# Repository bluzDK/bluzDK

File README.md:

Bluz DK Hardware Files
==========
Bluz is a Development Kit (DK) that implements the Wiring language and talks to the [Particle](https://www.particle.io/) cloud through Bluetooth Low Energy. It can be accessed through a REST API and programmed from a Web IDE.

These files have been made available online through a [Creative Commons Attribution-ShareAlike 3.0](http://creativecommons.org/licenses/by-sa/3.0/) license.

You are welcome to distribute, remix, and use these files for commercial purposes. If you do so, please attribute the original design to Bluz both on the website and on the physical packaging of the product or in the instruction manual. All derivative works must be published under the same or a similar license.

All items are subject to change over time as the product is designed, so make sure you are always looking at the latest information by pulling often.

##Sections
<b>BOM</b>: Current Bill of Materials for bluz.

<b>Datasheets</b>: Datasheets for all major parts on the board, including the nrf51822 and the MDBT40 module that it uses.

<b>HW Design</b>: Schematics, board layouts, and other design files.

<b>HW Libraries</b>: Eagle CAD libraries for the components used on Bluz DK.

<b>Pin Mapping</b>: Pin mapping diagram for Bluz.

##Tech Specs
<p>Hardware</p>
<ul>
    <li>Nordic Semiconductor nRF51822 SoC</li>
    <li>ARM Cortex M0, 16MHz</li>
    <li>32KB RAM, 256KB FLASH</li>
    <li>Bluetooth LE 4.1</li>
    <li>10 bit ADC</li>
    <li>256KB External FLASH</li>
    <li>3.0V-6V (3.3V compatible)</li>
</ul>
<p>Power Consumption</p>
<ul>
    <li>Connected/Standby: 60uA</li>
    <li>Transmitting Max: 18mA</li>
</ul>
<p>Typical Range (subject to environment):</p>
<ul>
    <li>Indoors: 60-100 feet</li>
    <li>Outdoors: 150-200 feet</li>
</ul>
<p>Software</p>
<ul>
    <li>Spark Web IDE</li>
    <li>Wiring (same as Arduino)</li>
    <li>Native C/C++ Programming</li>
    <li>GCC ARM</li>
    <li>Assembly (if you're that bold)</li>
</ul>
<p>Cloud</p>
<ul>
    <li>Spark Connected</li>
    <li>IFTTT Integrated</li>
    <li>IPv6 Support</li>
    <li>Remote programmable through Spark Cloud</li>
    <li>Control via REST API</li>
</ul>

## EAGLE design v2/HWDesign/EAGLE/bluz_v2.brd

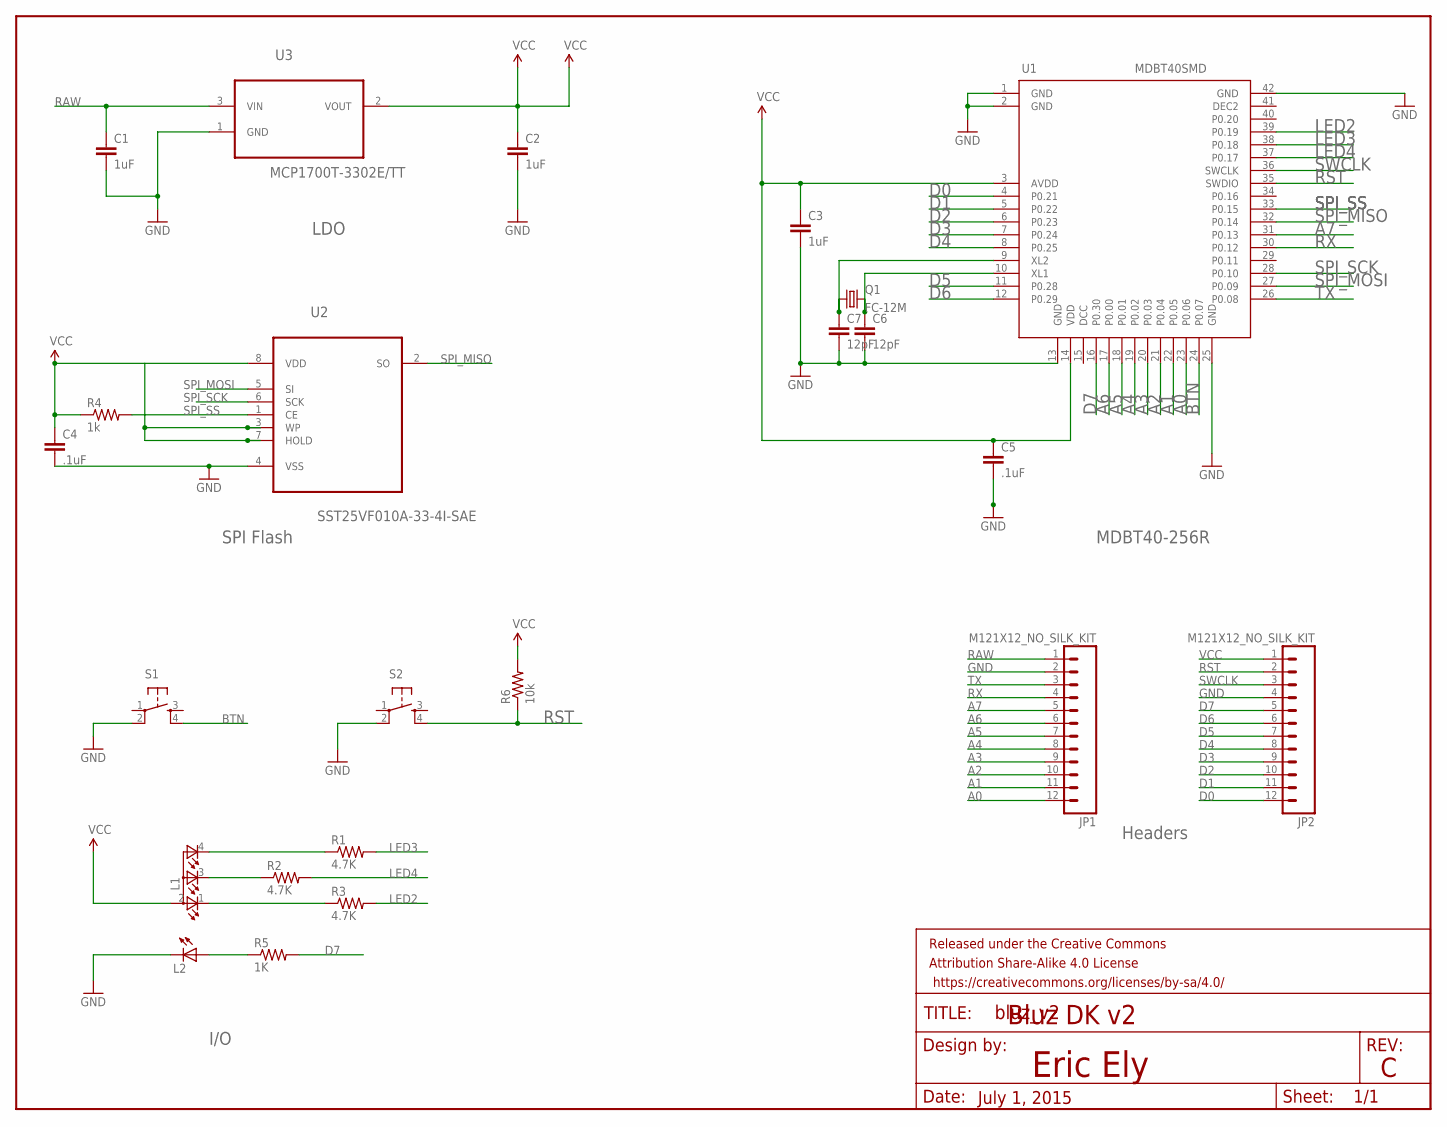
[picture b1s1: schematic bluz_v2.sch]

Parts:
C1, C2, C3: 1uF; 0603-CAP
C4, C5: .1uF; 0603-CAP
C6, C7: 12pF; 0603-CAP
FRAME1: FRAME-LETTER; CREATIVE_COMMONS
JP1, JP2: M121X12_NO_SILK_KIT; 1X12_NO_SILK_KIT
L1: TOPLED-3PLCC; P-LCC-4-3
L2: LEDCHIP-LED0603; CHIP-LED0603
Q1: FC-12M
R1, R2, R3: 4.7K; 0603-RES
R4: 1k; 0603-RES
R5: 1K; 0603-RES
R6: 10k; 0603-RES
S1, S2: TAC_SWITCHSMD; TACTILE_SWITCH_SMD
U1: MDBT40SMD; MDBT40
U2: SST25VF010A-33-4I-SAE; SOIC127P600X175-8N
U3: MCP1700T-3302E/TT; SOT95P237X112-3N

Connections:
A0: JP1.12, U1.23 (P0.06)
A1: JP1.11, U1.22 (P0.05)
A2: JP1.10, U1.21 (P0.04)
A3: JP1.9, U1.20 (P0.03)
A4: JP1.8, U1.19 (P0.02)
A5: JP1.7, U1.18 (P0.01)
A6: JP1.6, U1.17 (P0.00)
A7: JP1.5, U1.31 (P0.13)
BTN: S1.4, U1.24 (P0.07)
D0: JP2.12, U1.4 (P0.21)
D1: JP2.11, U1.5 (P0.22)
D2: JP2.10, U1.6 (P0.23)
D3: JP2.9, U1.7 (P0.24)
D4: JP2.8, U1.8 (P0.25)
D5: JP2.7, U1.11 (P0.28)
D6: JP2.6, U1.12 (P0.29)
D7: JP2.5, R5.2, U1.16 (P0.30)
GND: C1.2, C2.2, C3.2, C4.2, C5.2, C6.2, C7.2, JP1.2, JP2.4, L2.C, S1.2, S2.2, U1.1 (GND), U1.2 (GND), U1.13 (GND), U1.25 (GND), U1.42 (GND), U2.4 (VSS), U3.1 (GND)
LED2: R3.2, U1.39 (P0.19)
LED3: R1.2, U1.38 (P0.18)
LED4: R2.2, U1.37 (P0.17)
unnamed: C7.1, Q1.1, U1.9 (XL2)
unnamed: C6.1, Q1.2, U1.10 (XL1)
unnamed: L2.A, R5.1
unnamed: L1.1 (CRED), R3.1
unnamed: L1.3 (CBLUE), R2.1
unnamed: L1.4 (CGREEN), R1.1
RAW: C1.1, JP1.1, U3.3 (VIN)
RST: JP2.2, R6.1, S2.4, U1.35 (SWDIO)
RX: JP1.4, U1.30 (P0.12)
SPI_MISO: U1.32 (P0.14), U2.2 (SO)
SPI_MOSI: U1.27 (P0.09), U2.5 (SI)
SPI_SCK: U1.28 (P0.10), U2.6 (SCK)
SPI_SS: R4.2, U1.33 (P0.15), U2.1 (CE)
SWCLK: JP2.3, U1.36 (SWCLK)
TX: JP1.3, U1.26 (P0.08)
VCC: C2.1, C3.1, C4.1, C5.1, JP2.1, L1.2 (A2), R4.1, R6.2, U1.3 (AVDD), U1.14 (VDD), U2.3 (WP), U2.7 (HOLD), U2.8 (VDD), U3.2 (VOUT)

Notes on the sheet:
LDO
SPI Flash
I/O
Headers
MDBT40-256R
Eric Ely
Bluz DK v2
July 1, 2015

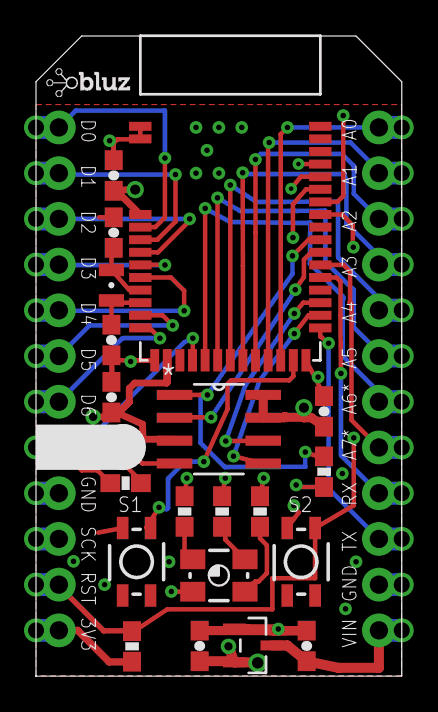
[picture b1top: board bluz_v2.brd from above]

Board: 2 copper layers, 20.3 x 35.6 mm, 26 parts (1 on the bottom side), 37 nets.

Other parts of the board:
U$1: BLUZE_LOGO_LOW_RES
U$2: MAKE_X2

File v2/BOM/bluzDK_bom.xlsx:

Part(s) | Package | Value | Description | Qty | Manufacturer | Mfg. Part Number | Data Sheet | Notes
U1 | SMD |  | nrf51822 module with 32K RAM | 1 | Raytac | MDBT40-256R | data
U2 | SOIC-8 | 2Mb | 2Mb SPI Flash | 1 | Microcip | SST25VF020B-80-4I-SAE | data
U3 | SOT-23-3 |  | Linear regulator with 3.3V output, 3.7V-6.0V Input | 1 | Microchip | MCP1700T-3302E/TT | data
Q1 |  | 32.768KHz | 20ppm, 9pF, 32.768KHz crystal | 1 |  | ABS06-32.768KHZ-9-T | data
C1-C3 | 0603 | 1uF | 0603 Package | 1 |  | CL10B105KP8NNNC | data
C4, C5 | 0603 | 0.1uF | 0603 Package | 3 |  | GRM188R71C104KA01D | data
C6, C7 | 0603 | 12pF | 0603 Package | 2 |  | CL10C120JB8NNNC | data
R1-R3 | 0603 | 4.7k Ohm | 4.7k Ohm | 3 |  | CRCW06034K70JNEA | data
R4-R5 | 0603 | 1k Ohm | 1k Ohm | 2 |  | CRCW06031K00FKEA | data
R6 | 0603 | 10k Ohm | 10k Ohm | 1 |  | CRCW060310K0FKEA | data
S1, S1 | SMD |  | 3.5mmx2.9mm Tactile Switch | 2 |  | EVP-AA202K | data
L1 | SMD |  | 3.2mm x 2.7m RGB LED | 1 |  | CLVBA-FKA-CAEDH8BBB7A363 | data
L2 | 0603 |  | White SMD LED | 1 |  | LW Q38G-Q1S1-3K6L-1 | data
JP1, JP2 | Thru |  | 0.1" 12-pin header | 2 |  | 68000-412HLF | data

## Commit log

2015-05-21 start uploading datasheets and hardware libraries
2015-05-21 first schematic
2015-05-21 Added BOM
2015-05-21 fixed typo
2015-05-27 add tech specs
2015-05-27 updated datasheet of SPI flash to the correct one, had an older version in there
2015-07-01 fix a few issues with capacitor values and placement
2015-07-02 updated schematic after routing. eagle cad files after first pass in routing
2015-07-02 cleaned up some issues. filled remaining top layer with ground
2015-07-03 change part number for LDO in BOM. update PCB. script for generating gerbers
2015-07-06 fix an issue on the PCB
2015-07-06 update SPI FLash part on BOM
2015-08-19 larger silkscreen. remove labels. copper on bottom of castellated edges. move buttons further in
2015-09-01 updated RGB LED to new part. changed resistors for new LED. updated labeling on bluz.
2015-09-13 updated BOM with correct RGB LED
2015-09-13 new mdbt40 datasheet
2015-09-13 cleanup some naming mistakes. properly labeled all capacitors
2015-10-06 programmer script to program and provision a new bluz PCB for the cloud
2015-10-07 make sure to save the provisioned ids to s file

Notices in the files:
parts and their libraries:
SparkFun-Capacitors: Licensing: Creative Commons ShareAlike 4.0 International - https://creativecommons.org/licenses/by-sa/4.0
SparkFun-Aesthetics: Released under the Creative Commons Attribution Share-Alike 4.0 License
SparkFun-Aesthetics: https://creativecommons.org/licenses/by-sa/4.0
